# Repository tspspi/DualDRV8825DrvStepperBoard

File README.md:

# Dual stepper driver board (ATMEGA328P, DRV8825)

This repository contains sourcefiles and schematics for a DRV8825 based
dual stepper driver board. The stepper control algorithm is implemented
on an ATMega328P. The code is compatible with avr-gcc (see Makefile) and
the Arduino IDE (one has to ```#define ARDUINO 1``` to use code for the
Arduino platform).

This controller is thought to be used in robotic and CNC applications.
Some features make it useable as cruise control controller for small
robots that use steppers instead of other brushed or brushless motors
and which may require precise control over speed / sometimes precise control
over their position.

Since the controller uses I2C it can be controlled from 3.3V and 5V
devices without any level shifters (if pullups are only present to 3.3V
but not 5V vcc).

__The controller is currently work in progress (but usable). Functions that
have been tested won't change behaviour__

__Correctness proof is currently work in progress__

The stepper driver can be controlled via I2C and supports:

* Running at a constant speed
* Accelerated linear movement from one position to another
  position (stop to stop) as needed in many CNC applications
* Hold position (enable drivers, no movement)
* Free-wheeling (disable drivers)
* Accelerating or decelerating to another speed
* Emergency stop / Emergency stop with hold

Additional features:

* Commands and status via I2C to support up to 127 stepper
  driver boards (i.e. up to 254 steppers) per I2C bus.
* Runtime modification of acceleration/deceleration as well as
  maximum speed.
* Runtime reconfiguration of microstepping
* A configurable depth command queue (default 10 commands per channel)
* Aborting running commands
* Keeping track of current position (if enabled - useful for CNC applications)
* Keeping track of current speed

* Static analysis using frama-c and ACSL annotation is used to proof that the
  code is free of many known common runtime errors, numeric overflows/underflows,
  does only access valid memory, etc. and fulfills some properties (proofed by
  using an proof assistant). This is currently work in progress.

## Implementation status of I2C commands

|  Command | Implemented | Tested | Description | Comments |
| --- | --- | --- | --- | --- |
| Group 0: Configuration |
| i2cCmd_GetAccelerateDecelerate  	|  Y | Y |  8 byte payload Slave -> Master + 1 Byte Status | |
| i2cCmd_SetAccelerateDecelerate  	|  Y |  |  8 Byte payload Master -> Slave |  | |
| i2cCmd_GetVMax  					|  Y |  |  4 byte payload Slave -> Master + 1 Byte Status |  | |
| i2cCmd_SetVMax  					|  Y |  |  4 Byte payload Mater -> Slave | |
| i2cCmd_GetAlpha  					|  Y |  |  4 Byte payload Slave -> Master + 1 Byte Status | |
| i2cCmd_SetAlpha  					|  Y |  |  4 Byte payload Master -> Slave | |
| i2cCmd_GetMicrostepping  			|  Y |  |  1 Byte payload Slave -> Master (2x 3 Bit) + 1 Byte Status | |
| i2cCmd_SetMicrostepping  			|  Y | Y |  1 Byte payload Master -> Slave | Note: Currently microstepping does __not__ rescale step size (alpha) automatically |
| i2cCmd_GetFault  					|  Y |  |  1 Byte payload Master -> Slave (IS status) | |
| i2cCmd_RecalculateConstants  		|  Y |  |  Used to trigger recalculation of all constants (expensive operation; system should be stopped) | |
| Group 1: Queue |
| i2cCmd_GetCommandQueueSize  		|  Y |  |  Get size (first byte) and unused entires (second byte) of command queue + 1 Byte status | |
| Group 2: Enqueue commands |
| i2cCmd_Queue_Sync  				|  |  |  Sync. point; 1 Byte Channel | |
| i2cCmd_Queue_ConstSpeed  			|  Y | Y |  Constant speed; 1 Byte Channel; 4 Byte Speed | |
| i2cCmd_Queue_MoveTo  				|  Y | Y |  Move To (accelerated); 1 Byte Channel; 4 Byte Position | |
| i2cCmd_Queue_ConstSpeedAccel  	| Y | Y |  Constant speed with acceleration/deceleration; 1 Byte channel; 4 Byte speed | |
| i2cCmd_Queue_Hold  				|  Y | Y |  Hold position; 1 byte channel | |
| i2cCmd_Queue_DisableDrv  			|  Y | Y |  Disable drivers; 1 byte channel (both have to be ordered to disable to be effective) | |
| Group 3: Execute commands immedately |
| i2cCmd_Exec_Sync  				|  |  |  Sync. point; 1 Byte Channel | |
| i2cCmd_Exec_ConstSpeed  			|  Y | Y |  Constant speed; 1 Byte Channel; 4 Byte Speed | |
| i2cCmd_Exec_MoveTo  				|  Y | Y |  Move To (accelerated); 1 Byte Channel; 4 Byte Position | |
| i2cCmd_Exec_ConstSpeedAccel  		| Y | Y |  Constant speed with acceleration/deceleration; 1 Byte channel; 4 Byte speed | |
| i2cCmd_Exec_Hold  				|  Y | Y |  Hold position; 1 byte channel | |
| i2cCmd_Exec_DisableDrv  			|  Y | Y |  Disable drivers; 1 byte channel (both have to be ordered to disable to be effective) | |
| Group F: Emergency commands |
| i2cCmd_EmergencyStop  			|  Y |  |  Keeps motors engaged but stopped | Drivers stay engaged so current will keep flowing |
| i2cCmd_EmergencyOff  				|  Y |  |  Keeps motors disabled | Since drivers are disabled motors are free to turn freely (inertia!) |

## Host library

The host library (controller) has been currenty implemented and tested
on FreeBSD (especially on the RaspberryPi platform). Example usage can
be seen in the ```controller/tests``` directory.

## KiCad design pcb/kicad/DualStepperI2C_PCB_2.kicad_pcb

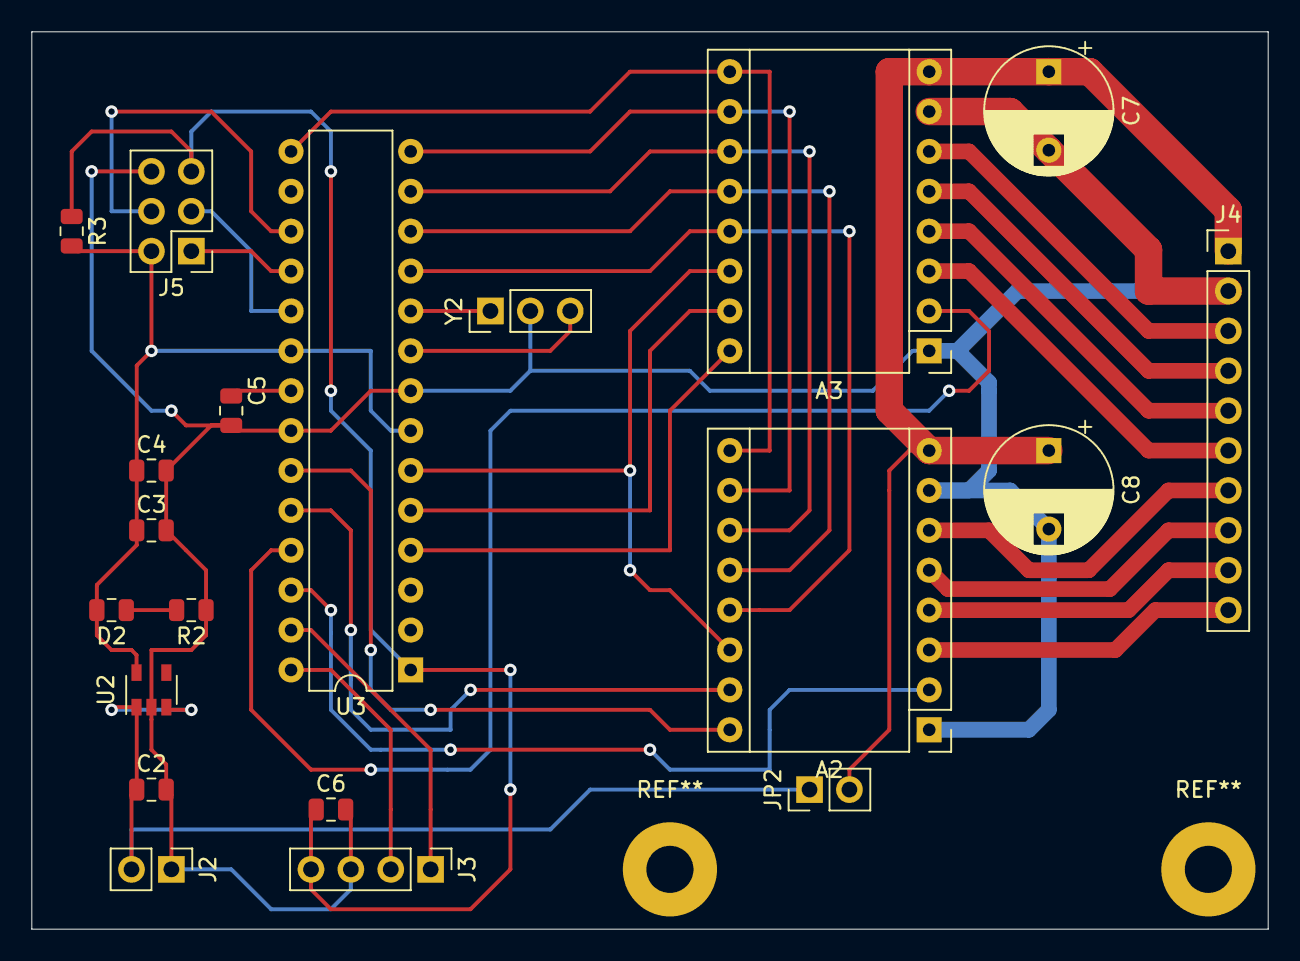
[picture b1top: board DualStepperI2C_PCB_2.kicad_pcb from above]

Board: 2 copper layers, 78.7 x 57.1 mm, 20 parts (0 on the bottom side), 34 nets.

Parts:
A2, A3: Pololu_Breakout_DRV8825; Pololu_Breakout-16_15.2x20.3mm
C2, C3: 10uF; C_0805_2012Metric
C4, C5, C6: 0.1uF; C_0805_2012Metric
C7, C8: 100uF; CP_Radial_D8.0mm_P5.00mm
D2: LED_Small; C_0805_2012Metric
J2: Screw_Terminal_01x02 PSULogic; PinHeader_1x02_P2.54mm_Vertical
J3: Screw_Terminal_01x04 (I2C, Rst); PinHeader_1x04_P2.54mm_Vertical
J4: Screw_Terminal_01x10 (Stepper); PinHeader_1x10_P2.54mm_Vertical
J5: Conn_02x03_ISP; PinHeader_2x03_P2.54mm_Vertical
JP2: Jumper_VMotVCC; PinHeader_1x02_P2.54mm_Vertical
R2, R3: 10k; R_0805_2012Metric
U2: MIC5205-5.0YM5; SOT-23-5
U3: ATmega328P-PU; DIP-28_W7.62mm
Y2: 16/20MHz; PinHeader_1x03_P2.54mm_Vertical

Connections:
+5V: C3.1, C4.1, D2.2, J5.2, R3.2, U2.5, U3.7, U3.20
GND: A2.1, A2.7, A3.1, A3.7, C2.2, C3.2, C4.2, C5.2, C6.2, C7.2, C8.2, J2.1, J3.3, J4.2, J5.6, R2.1, U2.2, U3.8, U3.22, Y2.2
unnamed: A2.2, U3.26
unnamed: A2.3, J4.10
unnamed: A2.4, J4.9
unnamed: A2.5, J4.8
unnamed: A2.6, J4.7
unnamed: A2.8, A3.8, C7.1, C8.1, J4.1, JP2.2
unnamed: A2.9, A3.9, U3.15
unnamed: A2.10, A3.10, U3.14
unnamed: A2.11, A3.11, U3.13
unnamed: A2.12, A3.12, U3.12
unnamed: A2.13, A3.13, U3.11
unnamed: A2.14, A3.14, U3.6
unnamed: A2.15, U3.24
unnamed: A2.16, U3.23
unnamed: A3.2, U3.25
unnamed: A3.3, J4.6
unnamed: A3.4, J4.5
unnamed: A3.5, J4.4
unnamed: A3.6, J4.3
unnamed: A3.15, U3.5
unnamed: A3.16, U3.4
unnamed: C2.1, J2.2, JP2.1, U2.1, U2.3
unnamed: C5.1, U3.21
unnamed: C6.1, J3.4, J5.5, R3.1, U3.1
unnamed: D2.1, R2.2
unnamed: J3.1, U3.27
unnamed: J3.2, U3.28
unnamed: J5.1, U3.18
unnamed: J5.3, U3.19
unnamed: J5.4, U3.17
unnamed: U3.9, Y2.3
unnamed: U3.10, Y2.1

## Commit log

2019-05-06 Added non-Arduino Version (if ARDUINO is not defined compiling works without Arduino libraries, if one wants to use Arduino IDE define ARDUINO as preprocessor variable
2019-05-06 Added README
2019-05-06 Added simplified BSD license
2019-05-07 Removed artifacts from Arduino libraries used during testing of the algorithm. The code now completely compiles without Arduino libraries with avr-gcc.
    Added I2C command definitions and I2C RX and TX queue handlers
    Implemented I2C commands (not tested):
    * i2cCmd_GetAccelerateDecelerate
    * i2cCmd_SetAccelerateDecelerate
    * i2cCmd_GetVMax
    * i2cCmd_SetVMax
2019-05-07 Removed tags from README that seem to be unsupported by github markdown renderer
2019-05-07 Replaced HTML table with markdown table
2019-05-07 Added support for constant speed and accelerated move steps functions via I2C
2019-05-07 Assigned correct operation to correct code
2019-05-08 Updated queuesize commnd to fit specification
2019-05-08 Added (work in progress) controller code for RaspberryPi
2019-05-08 Added currently available commands to command module. Verify serdes of floats!
2019-05-09 Some bugfixes
2019-05-10 Continued development
2019-05-11 Fixed I2C problem
    Fixed the problem of I2C messages arriving during steppers
    running. The TIMER2_COMPA_VECT routine took too long for TWI
    events to be handeled as required. Stepper steps are now triggered
    by setting an timer expired flag in the TIMER2_COMPA_VECT and
    polling in the main loop - likewise for received TWI messages.
    Note that this of course means that there is always the potential
2019-05-11 Updated test program to try a more complicated pattern of accelerated movements
2019-05-11 Some bugfixes (I2C transmit) and added support for exec commands for constant speed and accelerated relative movement
2019-05-11 Added support for reading and writing microstep configuration
2019-05-11 Added support for FAULT pins
2019-05-11 Updated README.md (implementation status)
2019-05-12 Patched I2C bug that prevented successful write-read transactions
2019-05-12 Reset fault state after readout
2019-05-13 Added second test to include stepper shutdown request
2019-05-13 Added support to disable stepper drivers during idle periods and re-enable on next command
2019-05-14 Fixed microstepping setting, added hold support, some bugfixes
2019-05-14 Added support for microstepping (setting) and added test 003 to test various microstepping settings
2019-05-15 - Added support for acceleration / deceleration to constant speed (from a previously moving state) - State variables for steppers are not required to be volatile any more since motion control has bee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
2019-05-15 Added support and test for acceleration / deceleration to constant speed
2019-05-15 Updated LICENSE
2019-05-16 Added schematic for board using DIP packages as much as possible and DRV8825 breakout boards
2019-05-20 Added support to query fault bits
2019-05-20 Added absolute positioning command and commands to read and write current absolute position
2019-05-20 Added controller commands for absolute positioning and position query/setting. Adding ability to execute position setting command immediately
2019-05-22 Added first revision PCB layout
2019-11-12 Added definition of M_PI for platforms that do not have M_PI defined (ex.: frama-c)
2019-11-15 * Added some annotations for frama-c's wp and wp-rte plugin (workd in progress, unfinished) * Fixed 4 RTEs in handleTimer2Interrupt * Added frama-c working directory to gitignore
2019-11-16 Continued ACSL annotations
2019-11-19 The following commands now delay their response till sufficient buffer space is available instead of failing silently:
    * i2cCmd_GetAccelerateDecelerate
    * i2cCmd_GetVMax
    * i2cCmd_GetAlpha
    * i2cCmd_GetMicrostepping
    * i2cCmd_GetAbsolutePosition
    * i2cCmd_GetCommandQueueSize
2019-11-20 Continued ACSL annotation for:
    * Various disjoint behaviors. They did use requires instead of assumes.
    * Added (incomplete) annotation to stepperSetup()
    * Added annotation for i2cRXDouble()
    * Added annotation for millis (modifies SREG, accesses systemMillis)
2019-11-20 Removed partial comment
2019-11-20 ACSL: Added axioms for the first bunch of hardware registers as well as the loop invariant in the timer interrupt handler
2019-11-24 Added more ACSL annotations, removed unnecessary constant c6
2019-11-26 Recalculated constants, updated ACSL, fixed some bugs
    Proofed that RTE doesn't locate any bugs in stepperPlanMovement_ConstantSpeed
    and stepperPlanMovement_AccelerateStopToStop if called within specified
    boundaries.
    Updated constants to match new calculations.
    Updated ACSL to provide all necessary preconditions and postconditions
    for both functions
2019-11-26 stepperPlanMovement_Disable: ACSL updated, all potential bugs located with RTE fixed
2019-11-26 stepperPlanMovement_Stop: ACSL updated
2019-11-26 stepperPlanSpeedChange: ACSL updated
2019-11-27 Fixed ACSL assumption for PCINT1_vect, added exclusion of FRAMAC_SKIP to cli() and sei() to prevent clobbering of memory in inline assembly clobber list and added C variant of microDelay loop for ver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
2019-11-27 Added make target for frama-c static analysis
2019-12-24 Modified makefile to generate CSV report during frama-c run
2020-12-06 Added missing ifdef
2020-12-06 Fixed invalid programmer type
